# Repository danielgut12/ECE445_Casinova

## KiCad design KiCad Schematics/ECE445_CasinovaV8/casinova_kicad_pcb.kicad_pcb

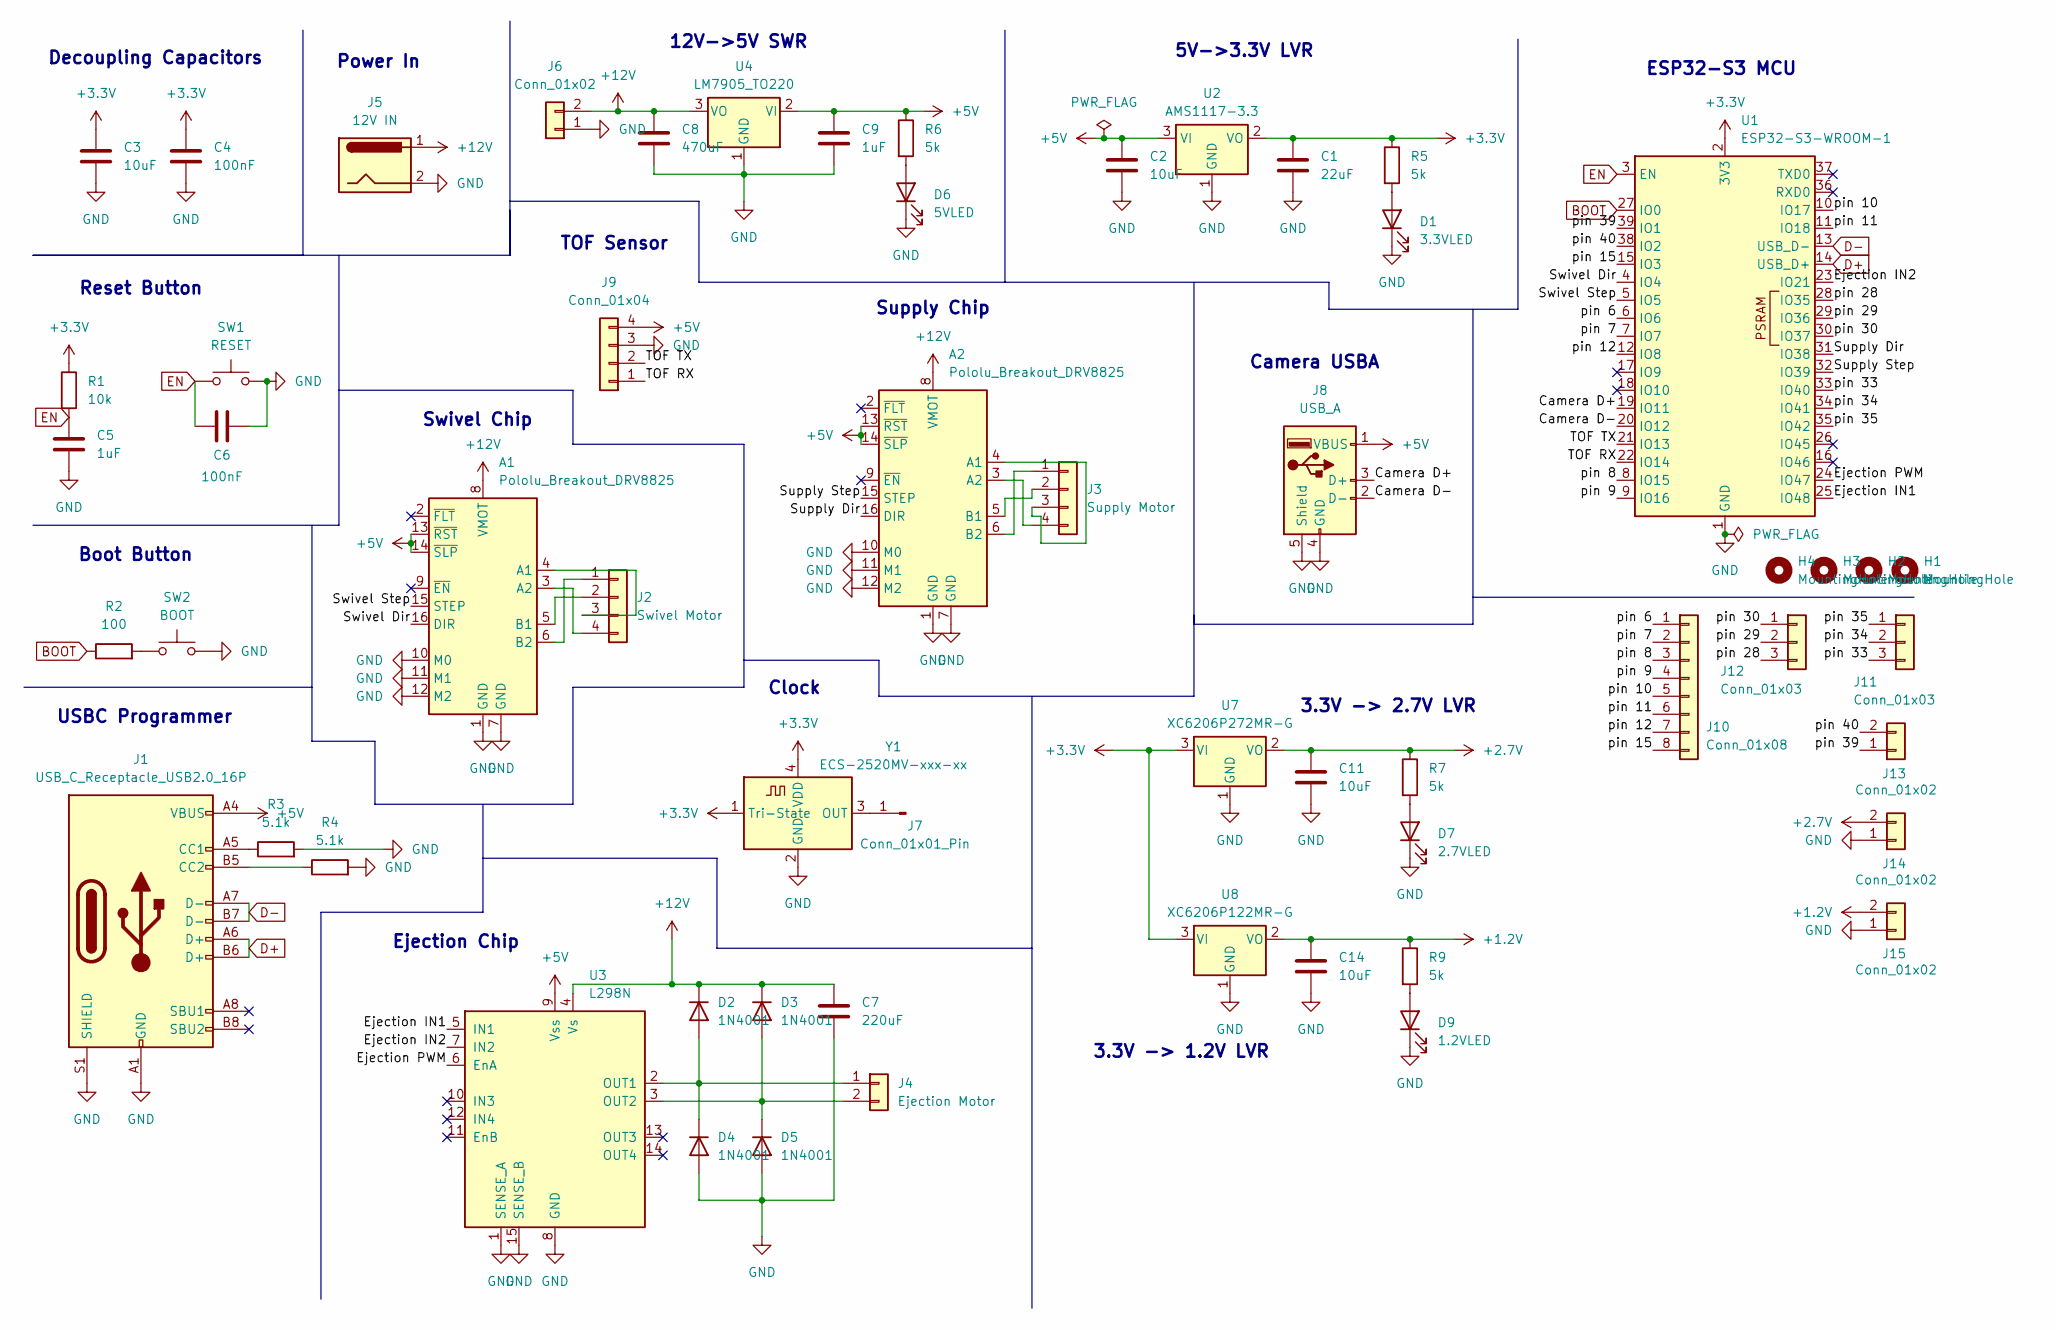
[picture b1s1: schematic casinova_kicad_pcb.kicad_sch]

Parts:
A1, A2: Pololu_Breakout_DRV8825; Pololu_Breakout-16_15.2x20.3mm
C1: 22uF; C_0805_2012Metric_Pad1.18x1.45mm_HandSolder
C2, C3, C11, C14: 10uF; C_0805_2012Metric_Pad1.18x1.45mm_HandSolder
C4, C6: 100nF; C_0805_2012Metric_Pad1.18x1.45mm_HandSolder
C5, C9: 1uF; C_0805_2012Metric_Pad1.18x1.45mm_HandSolder
C7: 220uF; C_0805_2012Metric_Pad1.18x1.45mm_HandSolder
C8: 470uF; CP_Radial_D8.0mm_P3.50mm
D1: 3.3VLED; LED_0805_2012Metric_Pad1.15x1.40mm_HandSolder
D2, D3, D4, D5: 1N4001; D_DO-41_SOD81_P10.16mm_Horizontal
D6: 5VLED; LED_0805_2012Metric_Pad1.15x1.40mm_HandSolder
D7: 2.7VLED; LED_0805_2012Metric_Pad1.15x1.40mm_HandSolder
D9: 1.2VLED; LED_0805_2012Metric_Pad1.15x1.40mm_HandSolder
H1, H2, H3, H4: MountingHole; MountingHole_3.2mm_M3
J1: USB_C_Receptacle_USB2.0_16P; USB_C_Receptacle_GCT_USB4085
J2: Swivel Motor; Molex_KK-254_AE-6410-04A_1x04_P2.54mm_Vertical
J3: Supply Motor; Molex_KK-254_AE-6410-04A_1x04_P2.54mm_Vertical
J4: Ejection Motor; Molex_KK-254_AE-6410-02A_1x02_P2.54mm_Vertical
J5: 12V IN; BarrelJack_SwitchcraftConxall_RAPC10U_Horizontal
J6, J13, J14, J15: Conn_01x02; Molex_KK-254_AE-6410-02A_1x02_P2.54mm_Vertical
J7: Conn_01x01_Pin; PinHeader_1x01_P1.00mm_Vertical
J8: USB_A; USB_A_Molex_48037-2200_Horizontal
J9: Conn_01x04; Molex_KK-254_AE-6410-04A_1x04_P2.54mm_Vertical
J10: Conn_01x08; Molex_KK-254_AE-6410-08A_1x08_P2.54mm_Vertical
J11, J12: Conn_01x03; Molex_KK-254_AE-6410-03A_1x03_P2.54mm_Vertical
R1: 10k; R_0805_2012Metric_Pad1.20x1.40mm_HandSolder
R2: 100; R_0805_2012Metric_Pad1.20x1.40mm_HandSolder
R3, R4: 5.1k; R_0805_2012Metric_Pad1.20x1.40mm_HandSolder
R5, R6, R7, R9: 5k; R_0805_2012Metric_Pad1.20x1.40mm_HandSolder
SW1: RESET; SW_SPST_PTS645
SW2: BOOT; SW_SPST_PTS645
U1: ESP32-S3-WROOM-1
U2: AMS1117-3.3; SOT-223-3_TabPin2
U3: L298N; TO-220-15_P2.54x5.08mm_StaggerOdd_Lead4.58mm_Vertical
U4: LM7905_TO220; TO-220-3_Vertical
U7: XC6206P272MR-G; SOT-23-3
U8: XC6206P122MR-G; SOT-23-3
Y1: ECS-2520MV-xxx-xx; Oscillator_SMD_ECS_2520MV-xxx-xx-4Pin_2.5x2.0mm

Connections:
+1.2V: C14.1, J15.2, R9.1, U8.2 (VO)
+2.7V: C11.1, J14.2, R7.1, U7.2 (VO)
+3.3V: C1.1, C3.1, C4.1, R1.1, R5.1, U1.2 (3V3), U2.2 (VO), U7.3 (VI), U8.3 (VI), Y1.1 (Tri-State), Y1.4 (VDD)
+5V: A1.13 (~RST), A1.14 (~SLP), A2.13 (~RST), A2.14 (~SLP), C2.1, C9.1, J1.A4 (VBUS), J1.A9 (VBUS), J1.B4 (VBUS), J1.B9 (VBUS), J8.1 (VBUS), J9.4, R6.1, U2.3 (VI), U3.9 (Vss), U4.2 (VI)
+12V: A1.8 (VMOT), A2.8 (VMOT), C7.1, C8.1, D2.1 (K), D3.1 (K), J5.1, J6.2, U3.4 (Vs), U4.3 (VO)
/Camera D+: J8.3 (D+), U1.19 (IO11)
/Camera D-: J8.2 (D-), U1.20 (IO12)
/Ejection IN1: U1.25 (IO48), U3.5 (IN1)
/Ejection IN2: U1.23 (IO21), U3.7 (IN2)
/Ejection PWM: U1.24 (IO47), U3.6 (EnA)
/Supply Dir: A2.16 (DIR), U1.31 (IO38)
/Supply Step: A2.15 (STEP), U1.32 (IO39)
/Swivel Dir: A1.16 (DIR), U1.4 (IO4)
/Swivel Step: A1.15 (STEP), U1.5 (IO5)
/TOF RX: J9.1, U1.22 (IO14)
/TOF TX: J9.2, U1.21 (IO13)
/pin 6: J10.1, U1.6 (IO6)
/pin 7: J10.2, U1.7 (IO7)
/pin 8: J10.3, U1.8 (IO15)
/pin 9: J10.4, U1.9 (IO16)
/pin 10: J10.5, U1.10 (IO17)
/pin 11: J10.6, U1.11 (IO18)
/pin 12: J10.7, U1.12 (IO8)
/pin 15: J10.8, U1.15 (IO3)
/pin 28: J12.3, U1.28 (IO35)
/pin 29: J12.2, U1.29 (IO36)
/pin 30: J12.1, U1.30 (IO37)
/pin 33: J11.3, U1.33 (IO40)
/pin 34: J11.2, U1.34 (IO41)
/pin 35: J11.1, U1.35 (IO42)
/pin 39: J13.1, U1.39 (IO1)
/pin 40: J13.2, U1.38 (IO2)
BOOT: R2.1, U1.27 (IO0)
D+: J1.A6 (D+), J1.B6 (D+), U1.14 (USB_D+)
D-: J1.A7 (D-), J1.B7 (D-), U1.13 (USB_D-)
EN: C5.1, C6.2, R1.2, SW1.1, U1.3 (EN)
GND: A1.1 (GND), A1.7 (GND), A1.10 (M0), A1.11 (M1), A1.12 (M2), A2.1 (GND), A2.7 (GND), A2.10 (M0), A2.11 (M1), A2.12 (M2), C1.2, C2.2, C3.2, C4.2, C5.2, C6.1, C7.2, C8.2, C9.2, C11.2, C14.2, D1.1 (K), D4.2 (A), D5.2 (A), D6.1 (K), D7.1 (K), D9.1 (K), J1.A1 (GND), J1.A12 (GND), J1.B1 (GND), J1.B12 (GND), J1.S1 (SHIELD), J5.2, J6.1, J8.4 (GND), J8.5 (Shield), J9.3, J14.1, J15.1, R3.2, R4.2, SW1.2, SW2.2, U1.1 (GND), U1.40 (GND), U1.41 (GND), U2.1 (GND), U3.1 (SENSE_A), U3.8 (GND), U3.15 (SENSE_B), U4.1 (GND), U7.1 (GND), U8.1 (GND), Y1.2 (GND)
unnamed: A1.4 (A1), J2.3
unnamed: A1.3 (A2), J2.4
unnamed: A1.5 (B1), J2.2
unnamed: A1.6 (B2), J2.1
unnamed: A2.4 (A1), J3.3
unnamed: A2.3 (A2), J3.4
unnamed: A2.5 (B1), J3.2
unnamed: A2.6 (B2), J3.1
unnamed: D1.2 (A), R5.2
unnamed: D2.2 (A), D4.1 (K), J4.1, U3.2 (OUT1)
unnamed: D3.2 (A), D5.1 (K), J4.2, U3.3 (OUT2)
unnamed: D6.2 (A), R6.2
unnamed: D7.2 (A), R7.2
unnamed: D9.2 (A), R9.2
unnamed: J1.A5 (CC1), R3.1
unnamed: J1.B5 (CC2), R4.1
unnamed: J7.1, Y1.3 (OUT)
unnamed: R2.2, SW2.1

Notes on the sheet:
Reset Button
5V->3.3V LVR
TOF Sensor
USBC Programmer
Supply Chip
3.3V -> 1.2V LVR
12V->5V SWR
Decoupling Capacitors
Ejection Chip
Clock
ESP32-S3 MCU
Boot Button
Camera USBA
Swivel Chip
Power In
3.3V -> 2.7V LVR

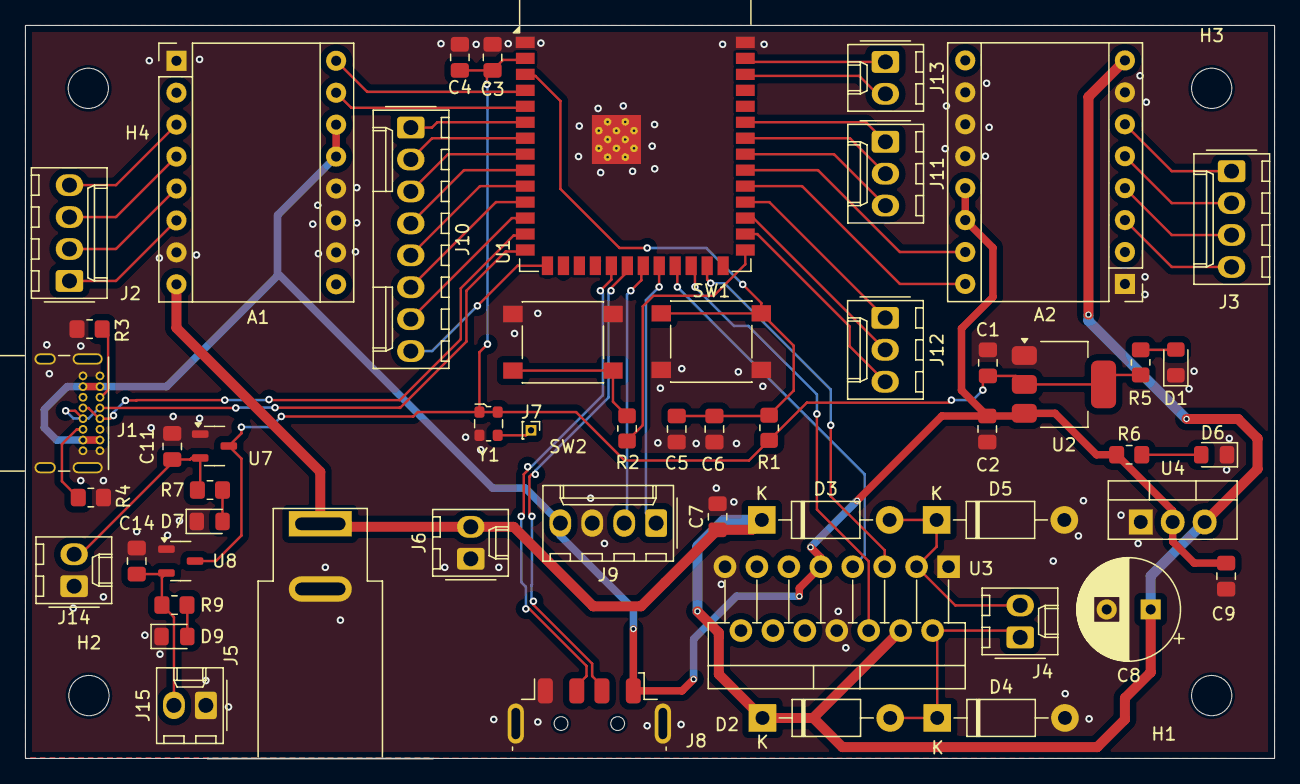
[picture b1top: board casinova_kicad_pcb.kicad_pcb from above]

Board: 2 copper layers, 99.3 x 58.3 mm, 57 parts (0 on the bottom side), 55 nets.

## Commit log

2025-03-04 March 1st Entry
2025-03-04 removed link to MOV
2025-03-04 fixing spacing in README
2025-03-04 fixed schematic png for README
2025-03-04 updated file structure
2025-03-04 test push
2025-03-04 created new notebook branch (matt)
2025-03-04 updated project notebook (matt)
2025-03-04 updated notebook 3-3-24
2025-03-04 updated matt 3-3-24
2025-03-05 update 3/4/25
2025-03-05 added TOF sensor code
2025-03-10 buncha a code drafts
2025-03-10 added instructions for psram
2025-03-11 added platformio stuff
2025-03-11 testing motor
2025-03-11 Demo code files uploaded
2025-03-27 basic camera code
2025-03-31 added all existing code
2025-04-01 grayscale image working
2025-04-10 image processing with webcam
2025-04-10 working image prcs with spcfc webcam setup paramters
2025-04-10 changed html and made changing parameters easier
2025-04-11 wifi still doesnt work
2025-04-12 started work on card logic
2025-04-14 redid camera org
2025-04-14 readded TOF sensor capabilities
2025-04-15 wifi capabilities and stuff
2025-04-15 simple wifi gpio 42 control
2025-04-15 prev chnages
2025-04-16 things
2025-04-16 demo
2025-04-16 streamlined capture image
2025-04-17 motor logic test
2025-04-21 ejection communicates with esp
2025-04-21 added swivel wifi function
2025-04-22 added poker logic WIP
2025-04-23 more game logic
2025-04-24 platformio fixed
2025-04-24 used camera images for processing
2025-04-24 works with web js
2025-04-24 deleted emsdk attempt
2025-04-25 added player name for front
2025-04-25 removed mjpeg streamer
2025-04-25 added debug page, made index main i/o page
2025-04-25 not working atm
2025-04-25 player ready system working
2025-04-25 fixed ready state on load
2025-04-26 more game logic changes
2025-04-26 poker games reset correctly after rounds
2025-04-26 cleaned up excess
2025-04-26 made ui look a lot better
2025-04-26 added commented hole card dealing
2025-04-26 folding logic + response works
2025-04-26 ready is toggleable
2025-04-27 tof sensor works again
2025-04-27 tof TRULY works now
2025-04-27 tof sensor updates to latest distance
2025-04-27 demo for card shooting
2025-04-27 queue motor runs on queue button function
2025-04-27 accell and decell for queue motor (more reliable)
2025-04-27 queue motor constant go demo
2025-04-27 added distance websocket
2025-04-27 finally updated lab notes
2025-04-27 added lab note media
2025-04-27 pcb stuff
2025-04-27 bad word
2025-04-27 removed poker stuff for now
2025-04-28 supply motor pcb demo code
2025-04-28 compatible with box
2025-04-28 added PWM features
2025-05-01 final demo
2025-05-08 finished notebook
2025-05-09 added all days
2025-05-09 added pictures to notebook
